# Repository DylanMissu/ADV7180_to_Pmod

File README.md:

# ADV7180_to_Pmod
These are pcb files for an analog camera block interface board based on the adv7180.

This board takes in analog video and outputs a digital ITU-R BT.656 video signal to the pmod ports. This can then be processed by an FPGA or a fast enough processor.

## Schematic

Schematic for the video converter.

## Pictures

| Front | Back |
|---|---|
| |  |

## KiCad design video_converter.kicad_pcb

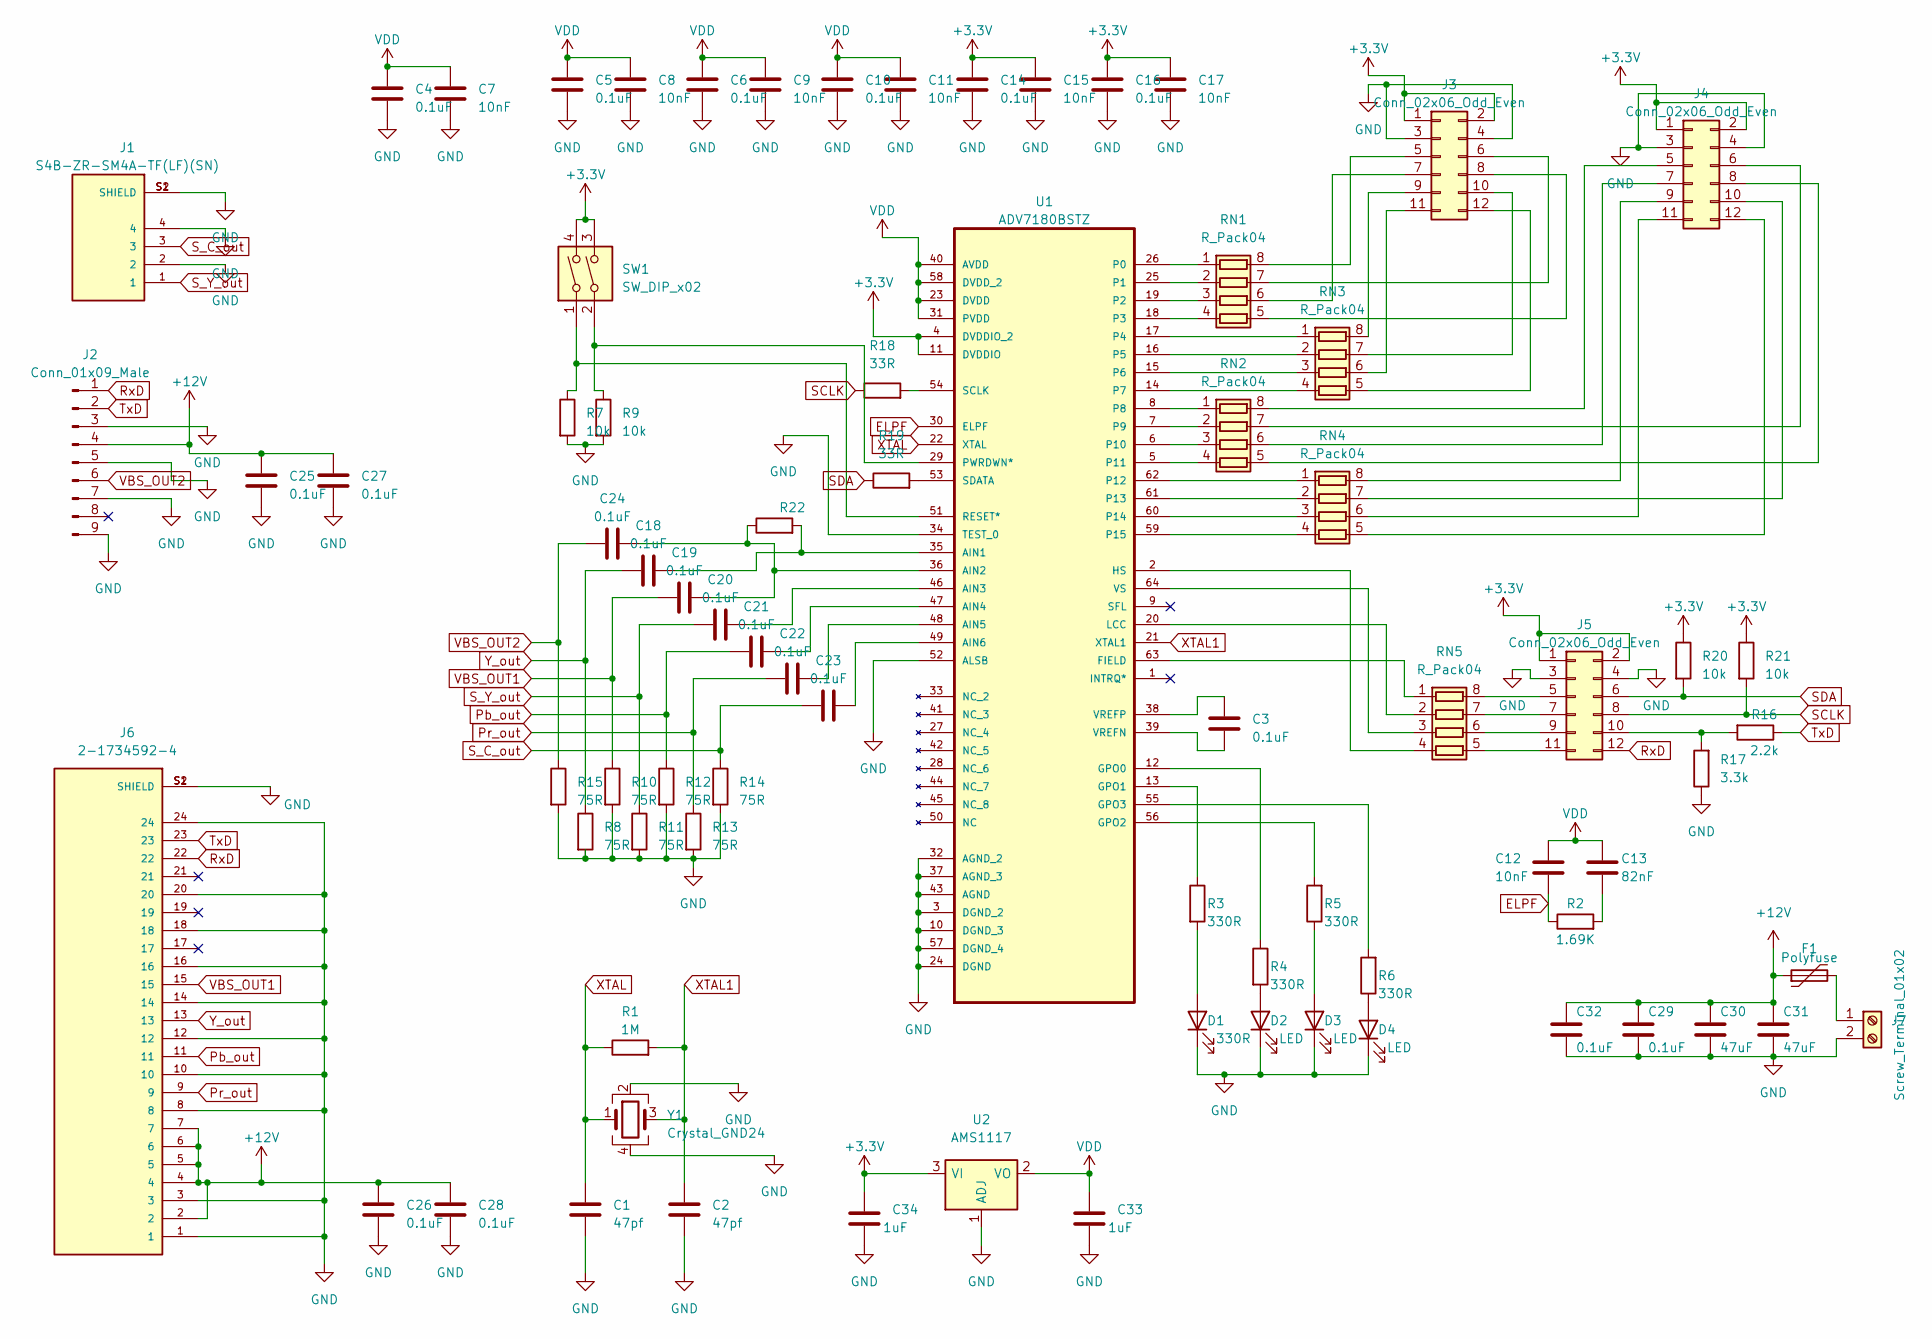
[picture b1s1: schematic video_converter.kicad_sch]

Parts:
C1, C2: 47pf; C_0603_1608Metric_Pad1.08x0.95mm_HandSolder
C3, C4, C5, C6, C10, C14, C16, C18, C19, C20, C21, C22, C23, C24, C25, C26, C27, C28, C29, C32: 0.1uF; C_0603_1608Metric_Pad1.08x0.95mm_HandSolder
C7, C8, C9, C11, C12, C15, C17: 10nF; C_0603_1608Metric_Pad1.08x0.95mm_HandSolder
C13: 82nF; C_0603_1608Metric_Pad1.08x0.95mm_HandSolder
C30, C31: 47uF; C_Elec_5x5.4
C33, C34: 1uF; C_0805_2012Metric_Pad1.18x1.45mm_HandSolder
D1: 330R; LED_0805_2012Metric_Pad1.15x1.40mm_HandSolder
D2, D3, D4: LED; LED_0805_2012Metric_Pad1.15x1.40mm_HandSolder
F1: Polyfuse; Fuse_1812_4532Metric_Pad1.30x3.40mm_HandSolder
J1: S4B-ZR-SM4A-TF(LF)(SN); JST_S4B-ZR-SM4A-TF(LF)(SN); PARTREV N/A
J2: Conn_01x09_Male; TE_84952-9_1x09-1MP_P1.0mm_Horizontal
J3, J4, J5: Conn_02x06_Odd_Even; PinHeader_2x06_P2.54mm_Horizontal
J6: 2-1734592-4; TE_2-1734592-4; PARTREV C
J7: Screw_Terminal_01x02; TerminalBlock_Phoenix_PT-1,5-2-3.5-H_1x02_P3.50mm_Horizontal
R1: 1M; R_0805_2012Metric_Pad1.20x1.40mm_HandSolder
R2: 1.69K; R_0805_2012Metric_Pad1.20x1.40mm_HandSolder
R3, R4, R5, R6: 330R; R_0805_2012Metric_Pad1.20x1.40mm_HandSolder
R7, R9, R20, R21: 10k; R_0805_2012Metric_Pad1.20x1.40mm_HandSolder
R8, R10, R11, R12, R13, R14, R15: 75R; R_0805_2012Metric_Pad1.20x1.40mm_HandSolder
R16: 2.2k; R_0805_2012Metric_Pad1.20x1.40mm_HandSolder
R17: 3.3k; R_0805_2012Metric_Pad1.20x1.40mm_HandSolder
R18, R19: 33R; R_0603_1608Metric_Pad0.98x0.95mm_HandSolder
R22: (no value)
RN1, RN2, RN3, RN4, RN5: R_Pack04; R_Array_Convex_4x0603
SW1: SW_DIP_x02; SW_DIP_SPSTx02_Slide_9.78x7.26mm_W7.62mm_P2.54mm
U1: ADV7180BSTZ; QFP50P1200X1200X160-64N; MPN ADV7180BSTZ
U2: AMS1117; SOT-223-3_TabPin2
Y1: Crystal_GND24; Crystal_SMD_Abracon_ABM8G-4Pin_3.2x2.5mm

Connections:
+3V3: C14.1, C15.1, C16.1, C17.1, C34.1, J3.1, J3.2, J4.1, J4.2, J5.1, J5.2, R20.1, R21.1, SW1.3, SW1.4, U1.4 (DVDDIO_2), U1.11 (DVDDIO), U2.3 (VI)
+12V: C25.1, C26.1, C27.1, C28.1, C29.1, C30.1, C31.1, C32.1, F1.1, J2.4, J6.2, J6.4, J6.5, J6.6, J6.7
ELPF: C12.1, R2.1, U1.30 (ELPF)
GND: C1.2, C2.2, C4.2, C5.2, C6.2, C7.2, C8.2, C9.2, C10.2, C11.2, C14.2, C15.2, C16.2, C17.2, C25.2, C26.2, C27.2, C28.2, C29.2, C30.2, C31.2, C32.2, C33.2, C34.2, D1.1 (K), D2.1 (K), D3.1 (K), D4.1 (K), J1.2, J1.4, J1.S1 (SHIELD), J1.S2 (SHIELD), J2.3, J2.5, J2.7, J2.9, J3.3, J3.4, J4.3, J4.4, J5.3, J5.4, J6.1, J6.3, J6.8, J6.10, J6.12, J6.14, J6.16, J6.18, J6.20, J6.24, J6.S1 (SHIELD), J6.S2 (SHIELD), J7.2, R7.2, R8.2, R9.2, R10.2, R11.2, R12.2, R13.2, R14.2, R15.2, R17.1, U1.3 (DGND_2), U1.10 (DGND_3), U1.24 (DGND), U1.32 (AGND_2), U1.34 (TEST_0), U1.37 (AGND_3), U1.43 (AGND), U1.52 (ALSB), U1.57 (DGND_4), U2.1 (ADJ), Y1.2, Y1.4
unnamed: C3.1, U1.38 (VREFP)
unnamed: C3.2, U1.39 (VREFN)
unnamed: C13.1, R2.2
unnamed: C18.2, R22.2, U1.35 (AIN1)
unnamed: C19.2, C24.2, R22.1, U1.36 (AIN2)
unnamed: C20.2, U1.46 (AIN3)
unnamed: C21.2, U1.47 (AIN4)
unnamed: C22.2, U1.48 (AIN5)
unnamed: C23.2, U1.49 (AIN6)
unnamed: D1.2 (A), R3.2
unnamed: D2.2 (A), R4.2
unnamed: D3.2 (A), R5.1
unnamed: D4.2 (A), R6.1
unnamed: F1.2, J7.1
unnamed: J3.5, RN1.8 (R1.2)
unnamed: J3.6, RN1.7 (R2.2)
unnamed: J3.7, RN1.6 (R3.2)
unnamed: J3.8, RN1.5 (R4.2)
unnamed: J3.9, RN3.8 (R1.2)
unnamed: J3.10, RN3.7 (R2.2)
unnamed: J3.11, RN3.6 (R3.2)
unnamed: J3.12, RN3.5 (R4.2)
unnamed: J4.5, RN2.8 (R1.2)
unnamed: J4.6, RN2.7 (R2.2)
unnamed: J4.7, RN2.6 (R3.2)
unnamed: J4.8, RN2.5 (R4.2)
unnamed: J4.9, RN4.8 (R1.2)
unnamed: J4.10, RN4.7 (R2.2)
unnamed: J4.11, RN4.6 (R3.2)
unnamed: J4.12, RN4.5 (R4.2)
unnamed: J5.5, RN5.8 (R1.2)
unnamed: J5.7, RN5.7 (R2.2)
unnamed: J5.9, RN5.6 (R3.2)
unnamed: J5.10, R16.2, R17.2
unnamed: J5.11, RN5.5 (R4.2)
unnamed: R3.1, U1.13 (GPO1)
unnamed: R4.1, U1.12 (GPO0)
unnamed: R5.2, U1.56 (GPO2)
unnamed: R6.2, U1.55 (GPO3)
unnamed: R7.1, SW1.1, U1.51 (RESET*)
unnamed: R9.1, SW1.2, U1.29 (PWRDWN*)
unnamed: R18.2, U1.54 (SCLK)
unnamed: R19.2, U1.53 (SDATA)
unnamed: RN1.1 (R1.1), U1.26 (P0)
unnamed: RN1.2 (R2.1), U1.25 (P1)
unnamed: RN1.3 (R3.1), U1.19 (P2)
unnamed: RN1.4 (R4.1), U1.18 (P3)
unnamed: RN2.1 (R1.1), U1.8
unnamed: RN2.2 (R2.1), U1.7 (P9)
unnamed: RN2.3 (R3.1), U1.6 (P10)
unnamed: RN2.4 (R4.1), U1.5 (P11)
unnamed: RN3.1 (R1.1), U1.17 (P4)
unnamed: RN3.2 (R2.1), U1.16 (P5)
unnamed: RN3.3 (R3.1), U1.15 (P6)
unnamed: RN3.4 (R4.1), U1.14 (P7)
unnamed: RN4.1 (R1.1), U1.62 (P12)
unnamed: RN4.2 (R2.1), U1.61 (P13)
unnamed: RN4.3 (R3.1), U1.60 (P14)
unnamed: RN4.4 (R4.1), U1.59 (P15)
unnamed: RN5.1 (R1.1), U1.63 (FIELD)
unnamed: RN5.2 (R2.1), U1.20 (LCC)
unnamed: RN5.3 (R3.1), U1.64 (VS)
unnamed: RN5.4 (R4.1), U1.2 (HS)
Pb_out: C21.1, J6.11, R12.1
Pr_out: C22.1, J6.9, R13.1
RxD: J2.1, J5.12, J6.22
SCLK: J5.8, R18.1, R21.2
SDA: J5.6, R19.1, R20.2
S_C_out: C23.1, J1.3, R14.1
S_Y_out: C20.1, J1.1, R11.1
TxD: J2.2, J6.23, R16.1
VBS_OUT1: C19.1, J6.15, R10.1
VBS_OUT2: C24.1, J2.6, R15.1
VDD: C4.1, C5.1, C6.1, C7.1, C8.1, C9.1, C10.1, C11.1, C12.2, C13.2, C33.1, U1.23 (DVDD), U1.31 (PVDD), U1.40 (AVDD), U1.58 (DVDD_2), U2.2 (VO)
XTAL: C1.1, R1.1, U1.22 (XTAL), Y1.1
XTAL1: C2.1, R1.2, U1.21 (XTAL1), Y1.3
Y_out: C18.1, J6.13, R8.1

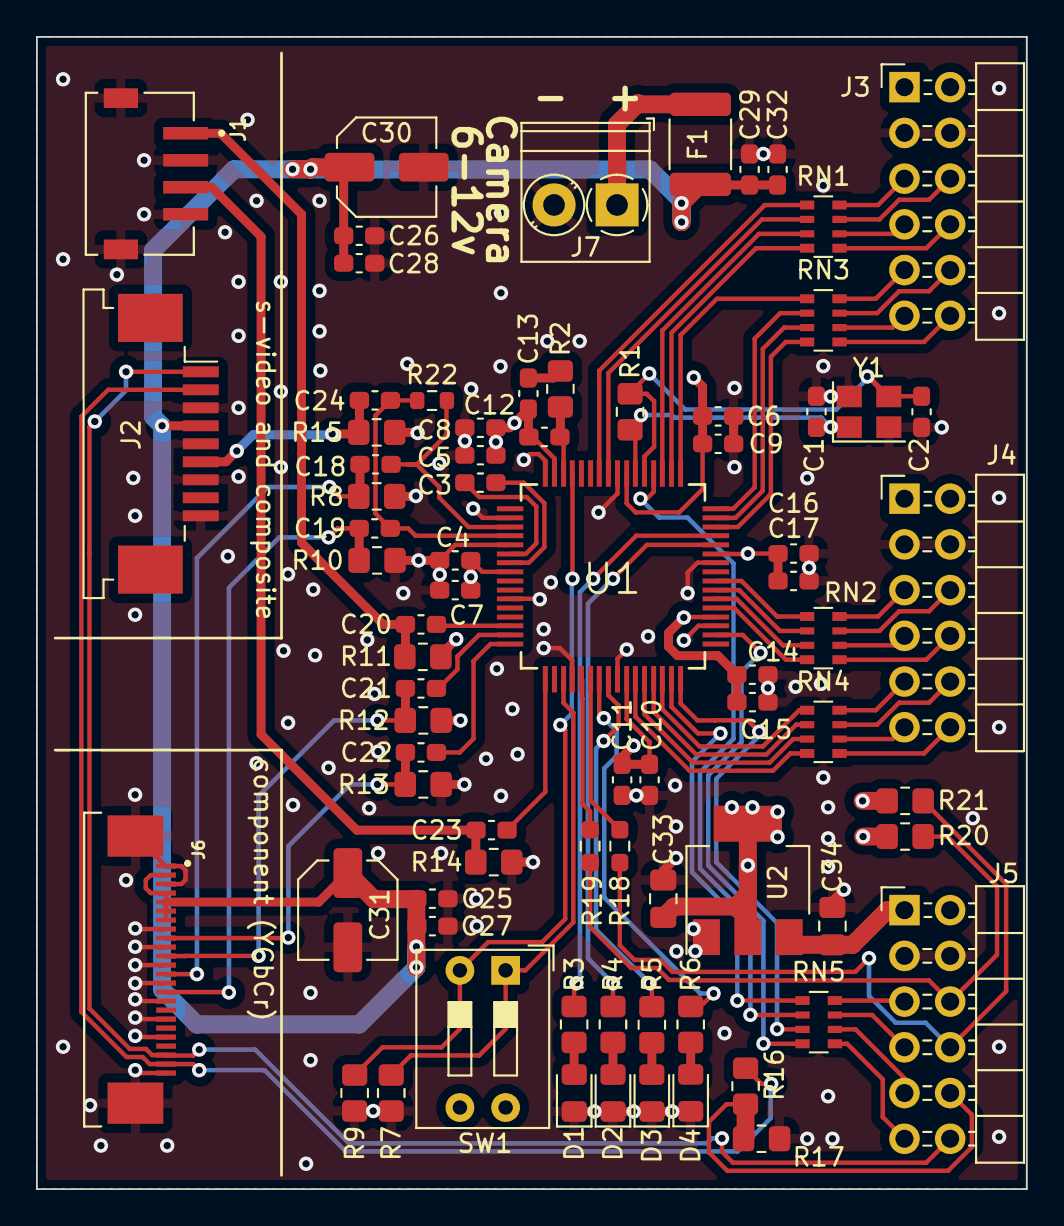
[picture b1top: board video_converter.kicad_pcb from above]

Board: 4 copper layers, 55.0 x 64.0 mm, 77 parts (0 on the bottom side), 81 nets.

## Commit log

2021-12-22 removed backups
2022-02-27 updated layout
2022-04-19 fixed bad routing
